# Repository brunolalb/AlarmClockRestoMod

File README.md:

# AlarmClockRestoMod
ESP32 Software for an Alarm Clock Resto Mod.

The idea is to use the components of an old alarm clock and replace the electronics with an ESP32, adding a lot of features to it. From an outside perspective, the clock will look as original as possible.

## Features

* WiFi connectivity
  * NTP time synchronization
  * Web server for advanced configuration
  * OTA updates
* Bluetooth connection from phone and to headphone/speaker
* Clock:
  * 7 segment display with dimming function
  * RTC for time keeping when power is out
* Alarms:
  * Configurable via web interface (advanced) or via buttons (only next alarm)
  * Configurable music or internet radio or buzzer for each alarm
  * Snooze function (delay configurable via web interface)
  * Vacation mode (turn off all alarms for a configurable period of time)
* Radio:
  * Internet radio stations configurable via web interface
  * Tuner button to switch between internet radio stations or playlists on microSD card
* microSD Card to store pre-owned Music, playlists and configuration files

## Components Overview
* Display is a 7 segment 4 digits with a TM1637, dimmable by software
* DS3231 for time keeping when power is out
* microSD Card with:
  * MP3 songs and playlists
  * Configuration file for radio stations (accepts internet radio station or playlist)
  * Configuration file for different alarms
* The tuner button of the alarm clock is a variable capacitor (10 - 500pF) read via a MPR121
  * Each frequency corresponds to an internet radio
* Bluetooth to connect to cellphone (play music from it) or to an external speaker/headphone
* Normal speaker connected via MAX98357A
* Buttons (Telefunken Digital Electronic 101):
  * 2 momentary switches to set time (Fast and slow)
  * 1 latching switch to turn on auto dimm/full light on display
  * 3 mutually-exclusive latching switches: show time, show next alarm (use the 2 momentary switches to set the alarm time) or "sleep mode" (turn on radio for 60min)
  * 1 momentary switch for sleep function (during alarm, press once to delay alarm in 5min, press twice to turn off alarm; during sleep mode, turn off radio)
  * 1 Volume slider (potentiometer)
  * 4 mutually-exclusive latching switches: turn on radio, turn off radio, alarm with radio, alarm with buzzing sound
  * 2 mutually-exclusive latching switches: radio corresponds to playlists, radio corresponds to internet radios
  * 1 momentary switch: one click (tries to connect to configured bluetooth speaker), two clicks (turns on bluetooth for phone to connect); if bluetooth connection is not successful after 1 min, turn off bluetooth
* Alarms:
  * fully configurable via web interface
  * choose days of the week
  * snooze time configurable
  * vacation mode
  * music and internet radio configured via web interface

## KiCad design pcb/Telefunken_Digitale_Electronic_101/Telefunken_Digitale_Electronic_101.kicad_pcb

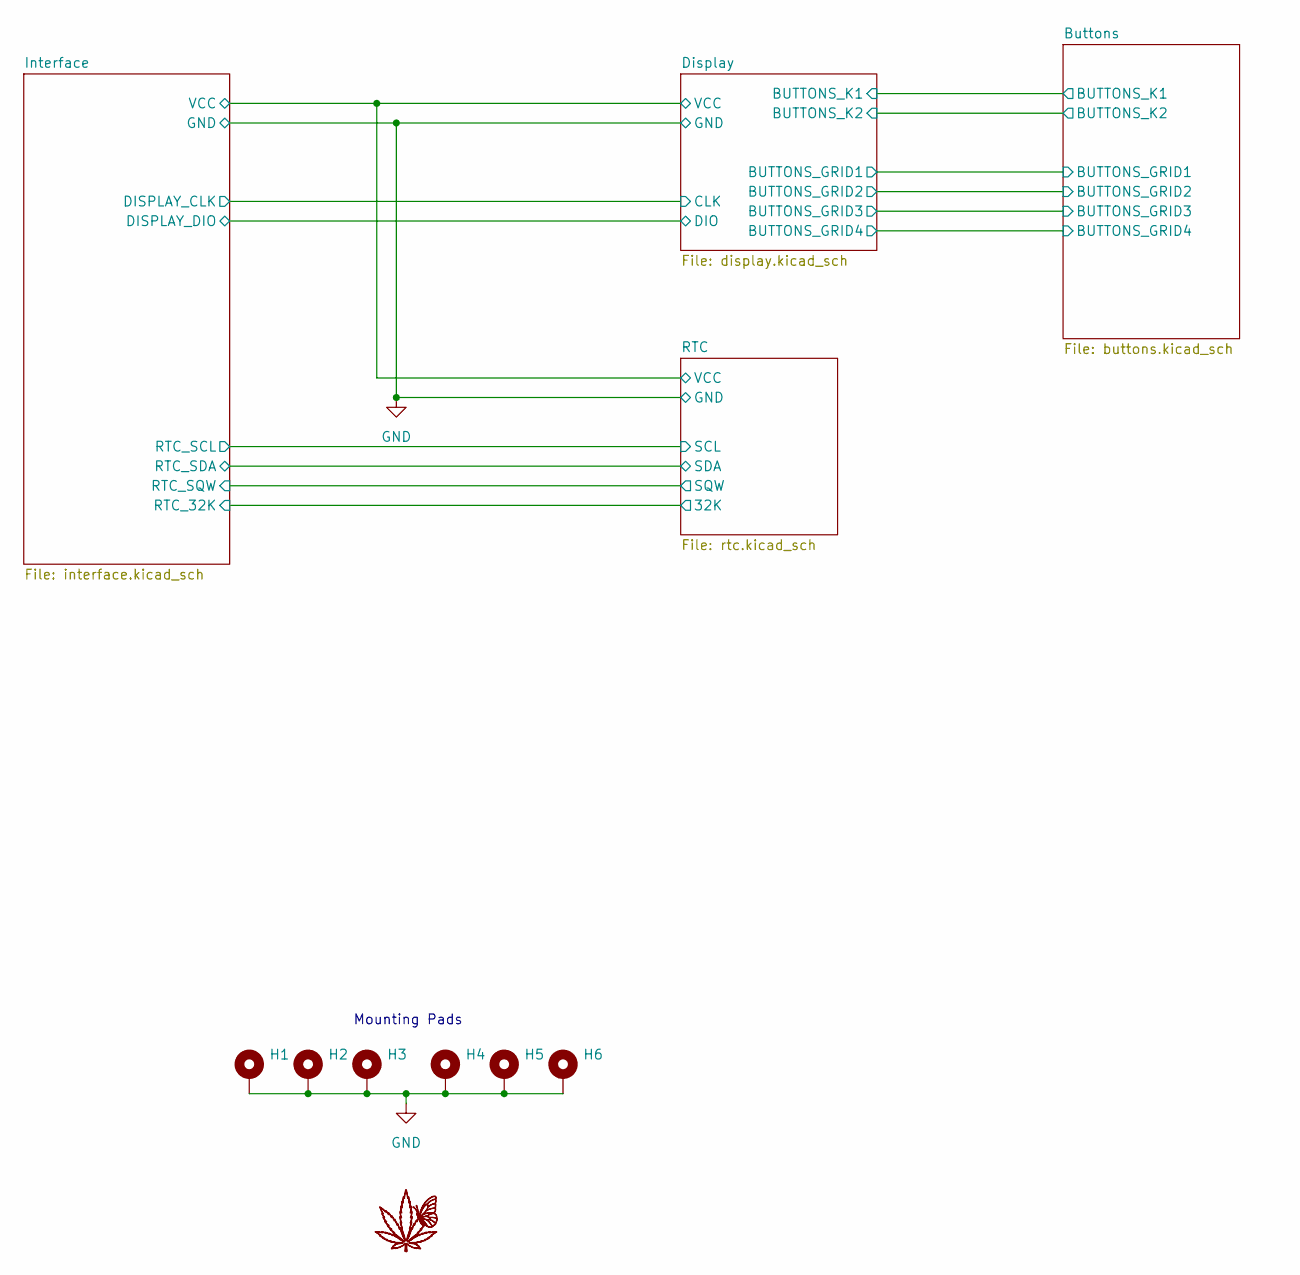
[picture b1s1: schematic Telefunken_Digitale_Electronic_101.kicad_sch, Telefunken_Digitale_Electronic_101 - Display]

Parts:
G1: LOGO
H1, H2, H3, H4, H5, H6: MountingHole_Pad_MP; BOARD_TO_BOARD_PAD_SMD

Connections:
GND: H1.MP (MP_MP), H2.MP (MP_MP), H3.MP (MP_MP), H4.MP (MP_MP), H5.MP (MP_MP), H6.MP (MP_MP); also elsewhere on the board

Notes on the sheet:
Mounting Pads

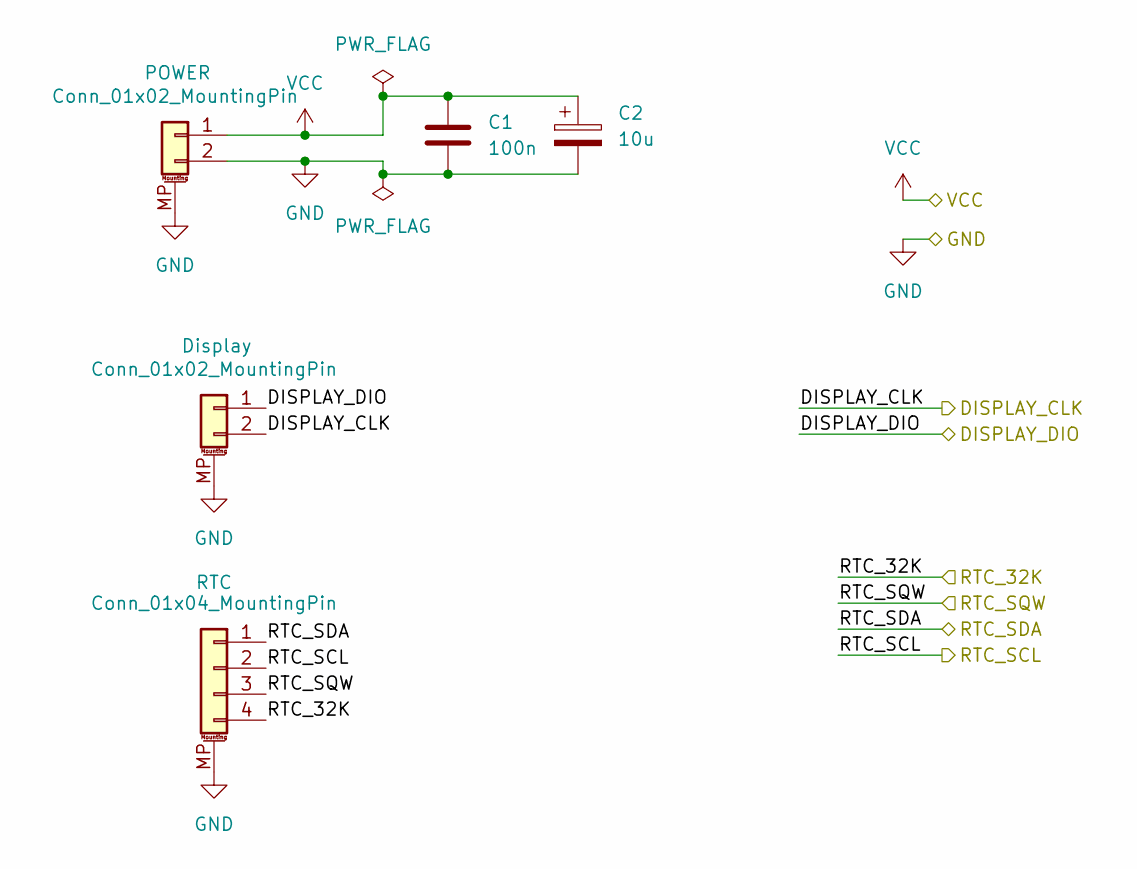
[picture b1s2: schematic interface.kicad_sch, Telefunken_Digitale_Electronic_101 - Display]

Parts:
C1: 100n; C_0603_1608Metric_Pad1.08x0.95mm_HandSolder
C2: 10u; CP_Radial_D4.0mm_P2.00mm
J1: Conn_01x02_MountingPin; JST_S2B-XH-SM4-TB
J2: Conn_01x02_MountingPin; Molex_PicoBlade_53261-0271_1x02-1MP_P1.25mm_Horizontal
J3: Conn_01x04_MountingPin; Molex_PicoBlade_53261-0471_1x04-1MP_P1.25mm_Horizontal

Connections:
/Display/CLK: J2.2; also elsewhere on the board
/Display/DIO: J2.1; also elsewhere on the board
/Interface/RTC_32K: J3.4; also elsewhere on the board
/Interface/RTC_SCL: J3.2; also elsewhere on the board
/Interface/RTC_SDA: J3.1; also elsewhere on the board
/Interface/RTC_SQW: J3.3; also elsewhere on the board
GND: C1.2, C2.2, J1.2, J1.MP (MountPin), J2.MP (MountPin), J3.MP (MountPin); also elsewhere on the board
VCC: C1.1, C2.1, J1.1; also elsewhere on the board

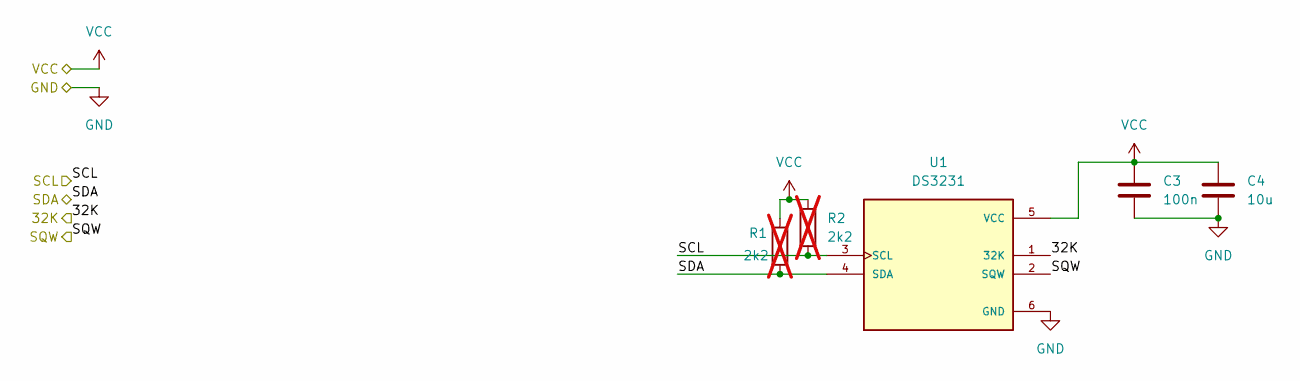
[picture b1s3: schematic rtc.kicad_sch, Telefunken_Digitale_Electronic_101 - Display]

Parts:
C3: 100n; C_0603_1608Metric_Pad1.08x0.95mm_HandSolder
C4: 10u; C_0805_2012Metric_Pad1.18x1.45mm_HandSolder
R1, R2: 2k2; R_0603_1608Metric_Pad0.98x0.95mm_HandSolder; not fitted
U1: DS3231

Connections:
/Interface/RTC_32K: U1.1 (32K); also elsewhere on the board
/Interface/RTC_SCL: R2.2, U1.3 (SCL); also elsewhere on the board
/Interface/RTC_SDA: R1.2, U1.4 (SDA); also elsewhere on the board
/Interface/RTC_SQW: U1.2 (SQW); also elsewhere on the board
GND: C3.2, C4.2, U1.6 (GND); also elsewhere on the board
VCC: C3.1, C4.1, R1.1, R2.1, U1.5 (VCC); also elsewhere on the board

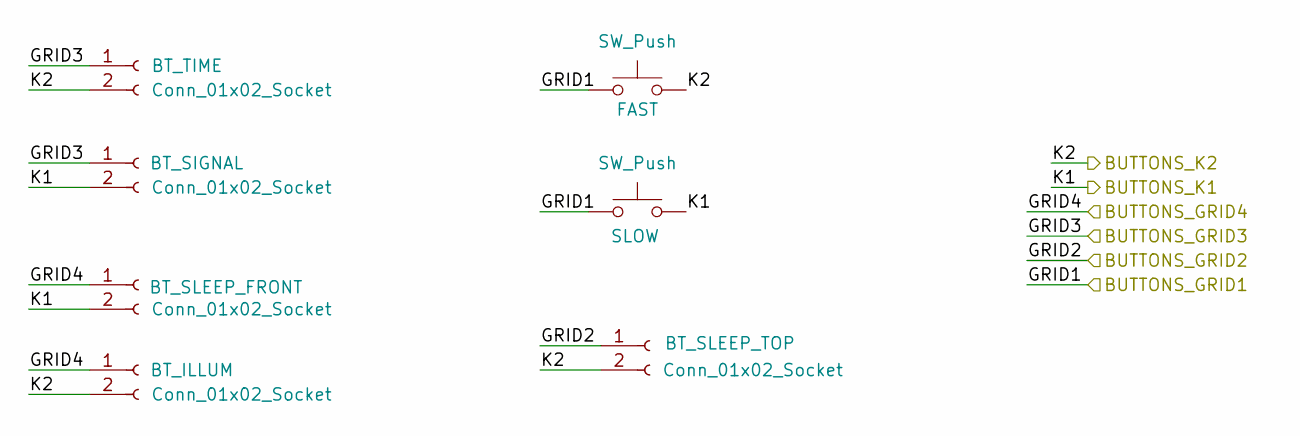
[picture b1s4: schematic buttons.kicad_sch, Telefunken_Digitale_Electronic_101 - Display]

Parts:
J4, J5, J6, J7, J8: Conn_01x02_Socket; PinSocket_1x02_P2.54mm_Vertical
SW1, SW2: SW_Push; TACT_SWITCH_3.2X4.2X2.5MM

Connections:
/Buttons/GRID1: SW1.1, SW2.1; also elsewhere on the board
/Buttons/GRID2: J8.1; also elsewhere on the board
/Buttons/GRID3: J4.1, J5.1; also elsewhere on the board
/Buttons/GRID4: J6.1, J7.1; also elsewhere on the board
/Buttons/K1: J5.2, J6.2, SW2.2; also elsewhere on the board
/Buttons/K2: J4.2, J7.2, J8.2, SW1.2; also elsewhere on the board

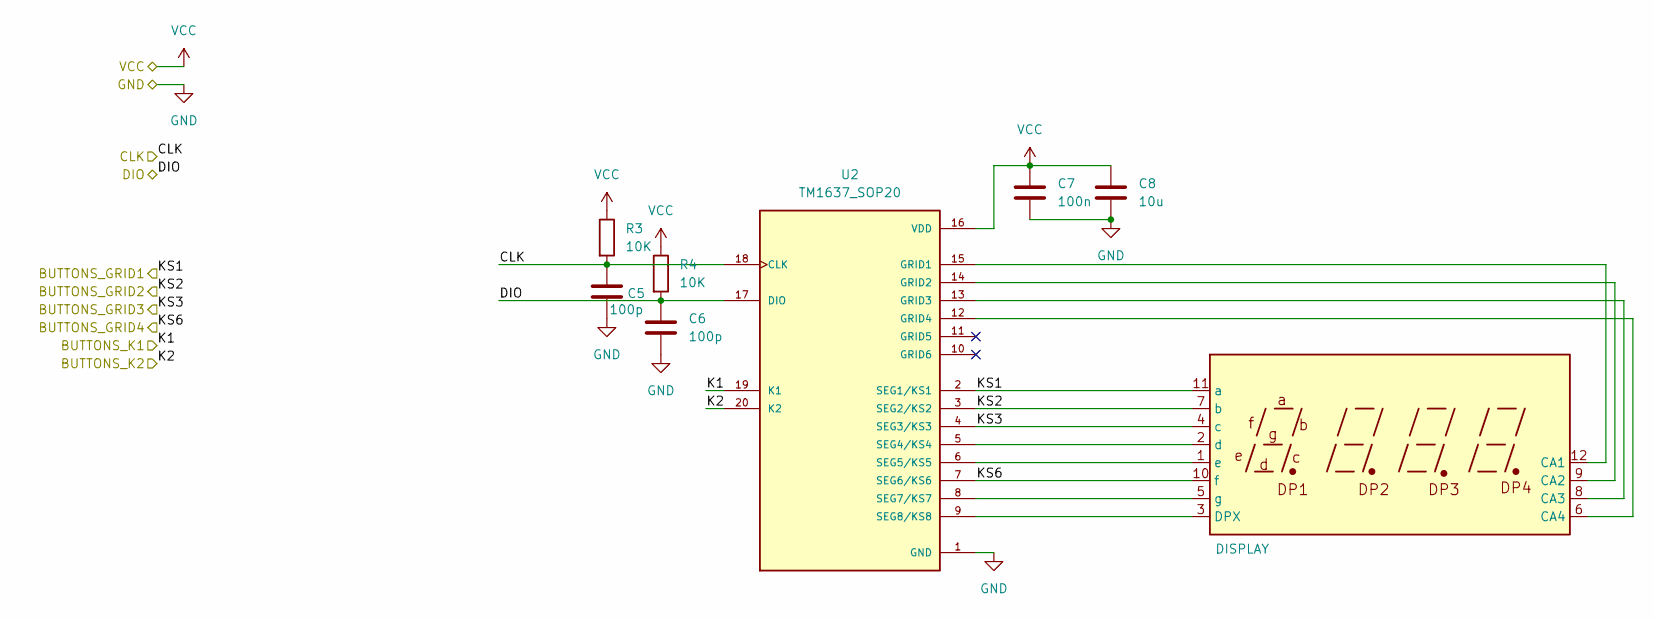
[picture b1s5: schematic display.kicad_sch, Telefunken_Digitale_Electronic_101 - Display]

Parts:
C5, C6: 100p; C_0603_1608Metric_Pad1.08x0.95mm_HandSolder
C7: 100n; C_0603_1608Metric_Pad1.08x0.95mm_HandSolder
C8: 10u; C_0805_2012Metric_Pad1.18x1.45mm_HandSolder
DISPLAY1: 8041BS-1
R3, R4: 10K; R_0603_1608Metric_Pad0.98x0.95mm_HandSolder
U2: TM1637_SOP20; SOIC127P1035X255-20N

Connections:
/Buttons/GRID1: DISPLAY1.11 (a), U2.2 (SEG1/KS1); also elsewhere on the board
/Buttons/GRID2: DISPLAY1.7 (b), U2.3 (SEG2/KS2); also elsewhere on the board
/Buttons/GRID3: DISPLAY1.4 (c), U2.4 (SEG3/KS3); also elsewhere on the board
/Buttons/GRID4: DISPLAY1.10 (f), U2.7 (SEG6/KS6); also elsewhere on the board
/Buttons/K1: U2.19 (K1); also elsewhere on the board
/Buttons/K2: U2.20 (K2); also elsewhere on the board
/Display/CLK: C5.1, R3.2, U2.18 (CLK); also elsewhere on the board
/Display/DIO: C6.1, R4.2, U2.17 (DIO); also elsewhere on the board
GND: C5.2, C6.2, C7.2, C8.2, U2.1 (GND); also elsewhere on the board
unnamed: DISPLAY1.12 (CA1), U2.15 (GRID1)
unnamed: DISPLAY1.9 (CA2), U2.14 (GRID2)
unnamed: DISPLAY1.8 (CA3), U2.13 (GRID3)
unnamed: DISPLAY1.6 (CA4), U2.12 (GRID4)
unnamed: DISPLAY1.3 (DPX), U2.9 (SEG8/KS8)
unnamed: DISPLAY1.2 (d), U2.5 (SEG4/KS4)
unnamed: DISPLAY1.1 (e), U2.6 (SEG5/KS5)
unnamed: DISPLAY1.5 (g), U2.8 (SEG7/KS7)
VCC: C7.1, C8.1, R3.1, R4.1, U2.16 (VDD); also elsewhere on the board

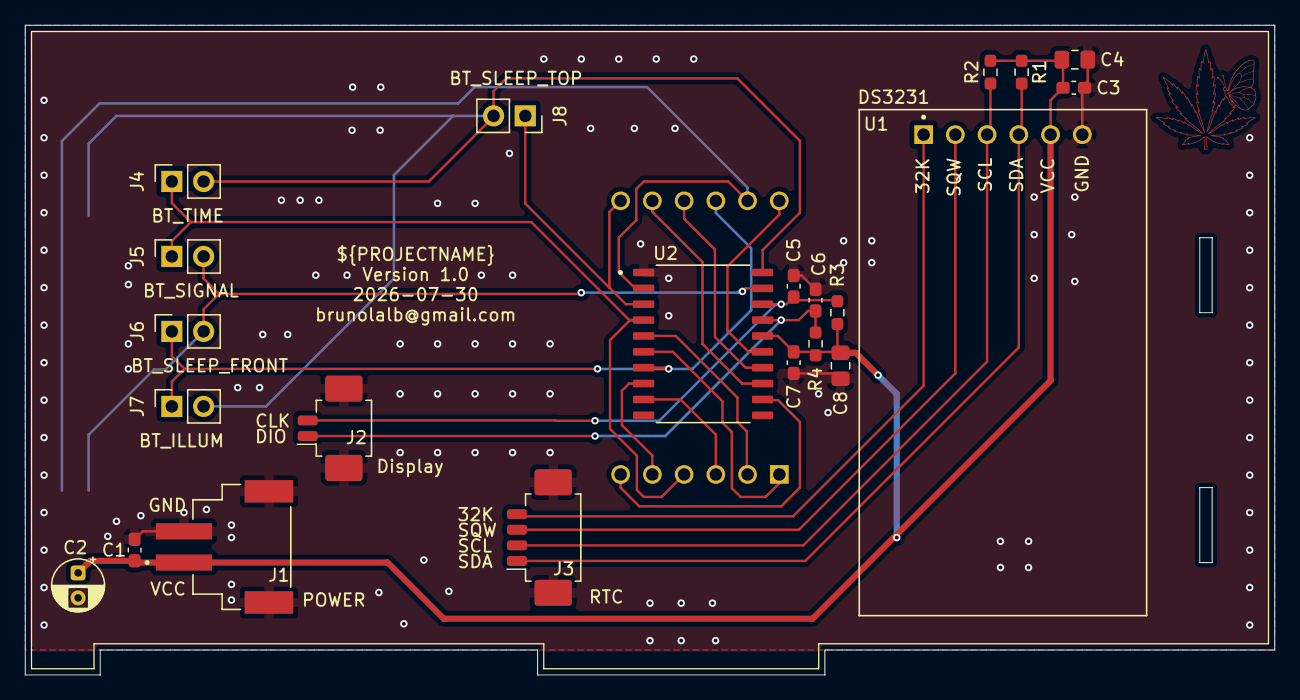
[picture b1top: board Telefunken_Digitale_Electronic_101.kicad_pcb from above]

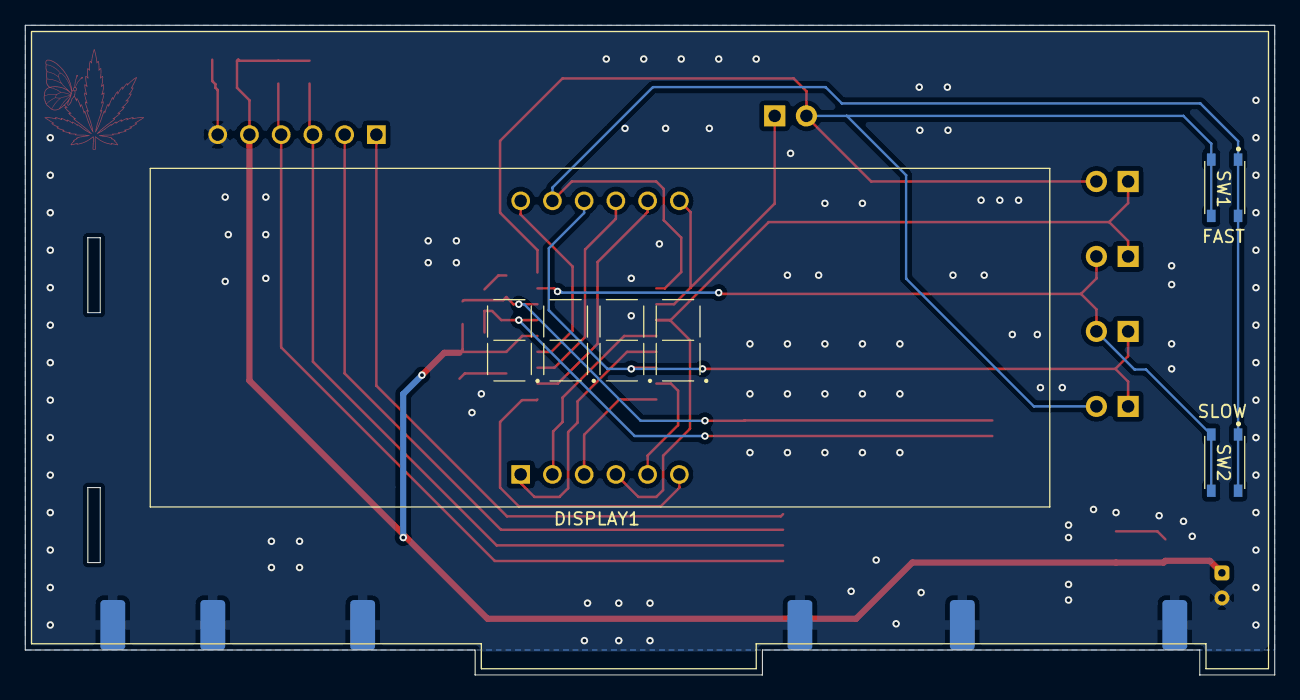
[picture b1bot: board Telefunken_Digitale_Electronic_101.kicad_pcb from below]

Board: 2 copper layers, 100.0 x 52.0 mm, 32 parts (9 on the bottom side), 22 nets.

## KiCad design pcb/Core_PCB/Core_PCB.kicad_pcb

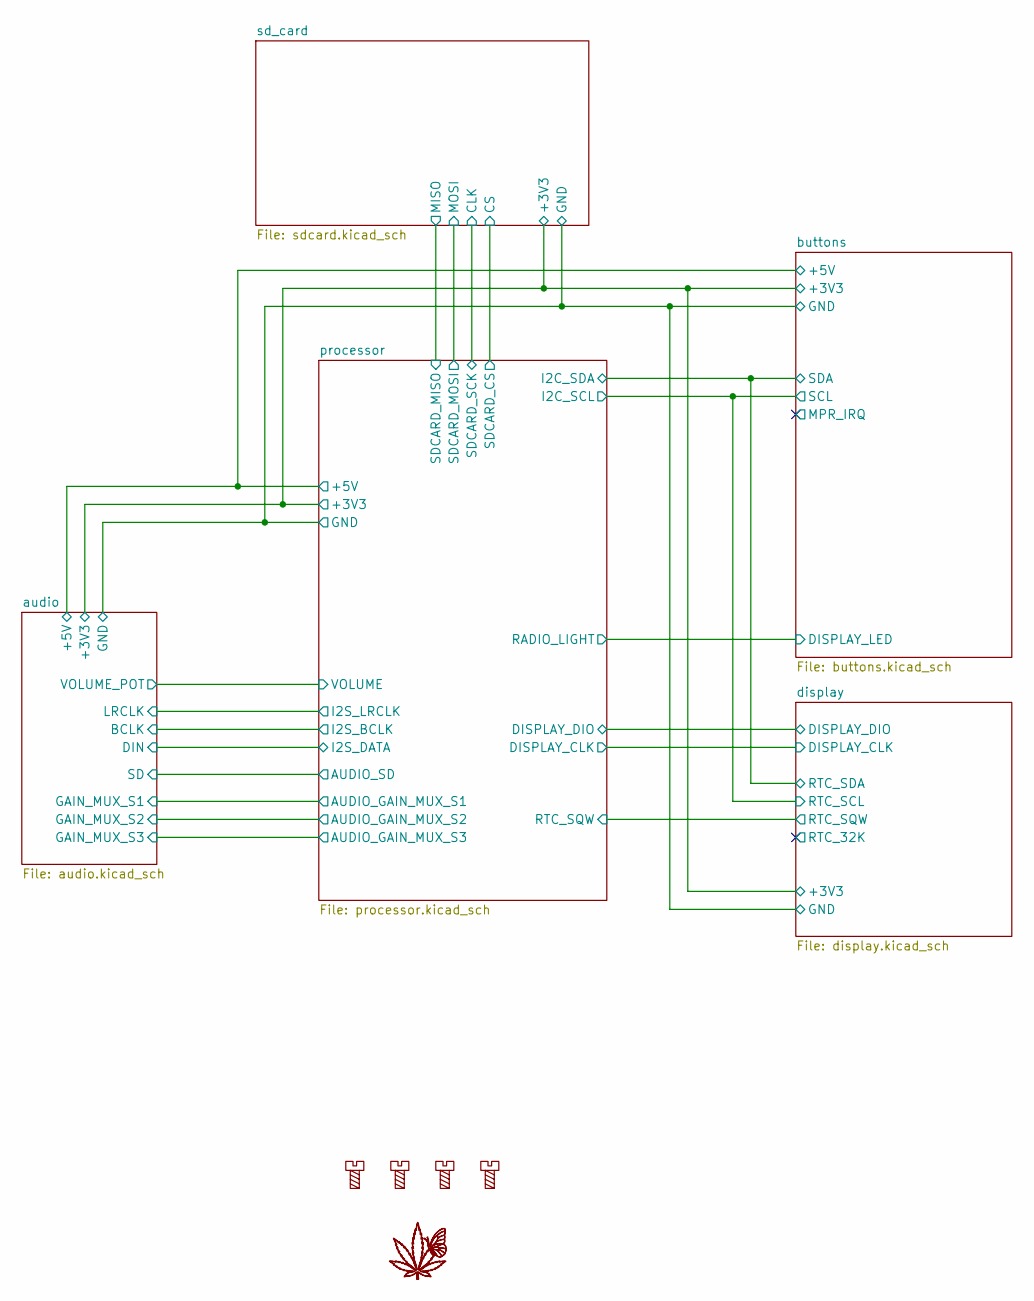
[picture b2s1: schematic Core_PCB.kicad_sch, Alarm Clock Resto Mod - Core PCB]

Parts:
G1: LOGO
H1, H2, H3, H4: MountingScrew; MountingHole_3.2mm_M3

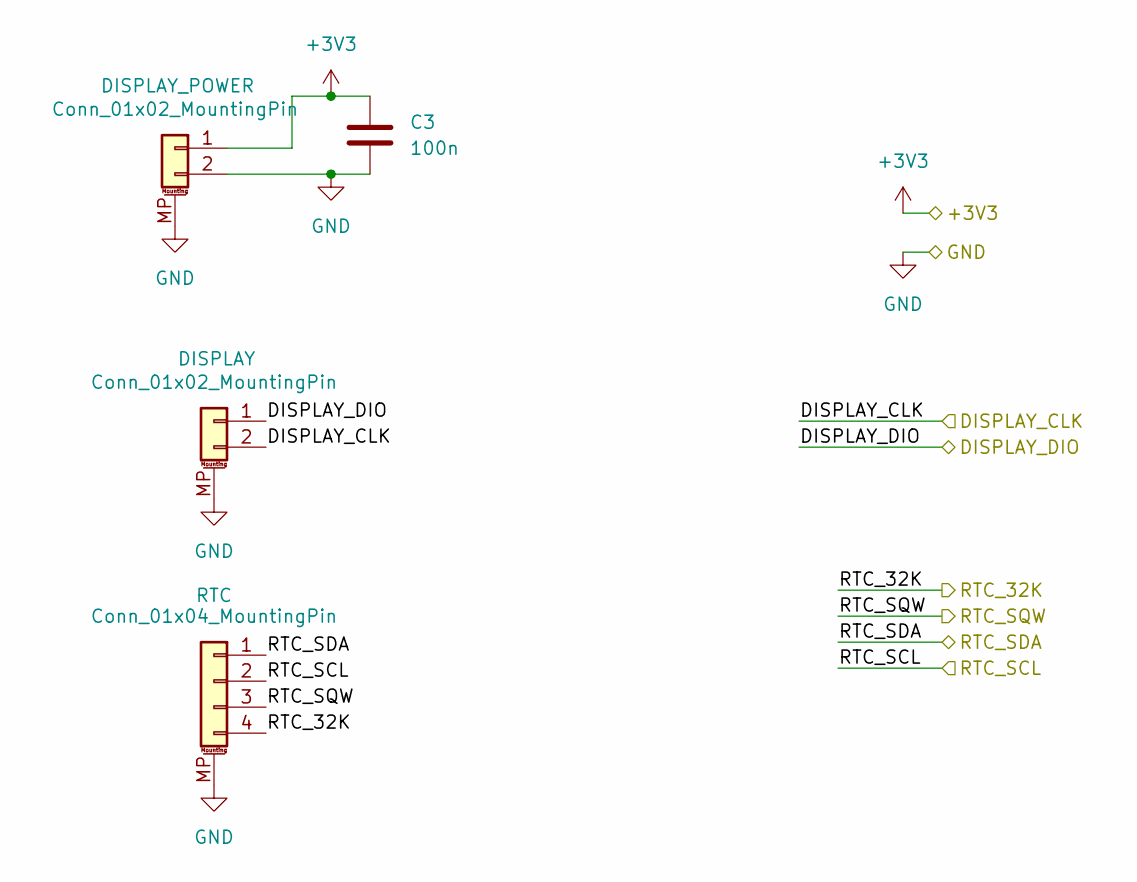
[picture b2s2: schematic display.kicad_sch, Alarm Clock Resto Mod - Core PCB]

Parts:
C3: 100n; C_0603_1608Metric_Pad1.08x0.95mm_HandSolder
J2: Conn_01x02_MountingPin; JST_S2B-XH-SM4-TB
J3: Conn_01x02_MountingPin; Molex_PicoBlade_53261-0271_1x02-1MP_P1.25mm_Horizontal
J4: Conn_01x04_MountingPin; Molex_PicoBlade_53261-0471_1x04-1MP_P1.25mm_Horizontal

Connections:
+3V3: C3.1, J2.1; also elsewhere on the board
/buttons/SCL: J4.2; also elsewhere on the board
/buttons/SDA: J4.1; also elsewhere on the board
/display/DISPLAY_CLK: J3.2; also elsewhere on the board
/display/DISPLAY_DIO: J3.1; also elsewhere on the board
/display/RTC_32K: J4.4
/display/RTC_SQW: J4.3; also elsewhere on the board
GND: C3.2, J2.2, J2.MP (MountPin), J3.MP (MountPin), J4.MP (MountPin); also elsewhere on the board

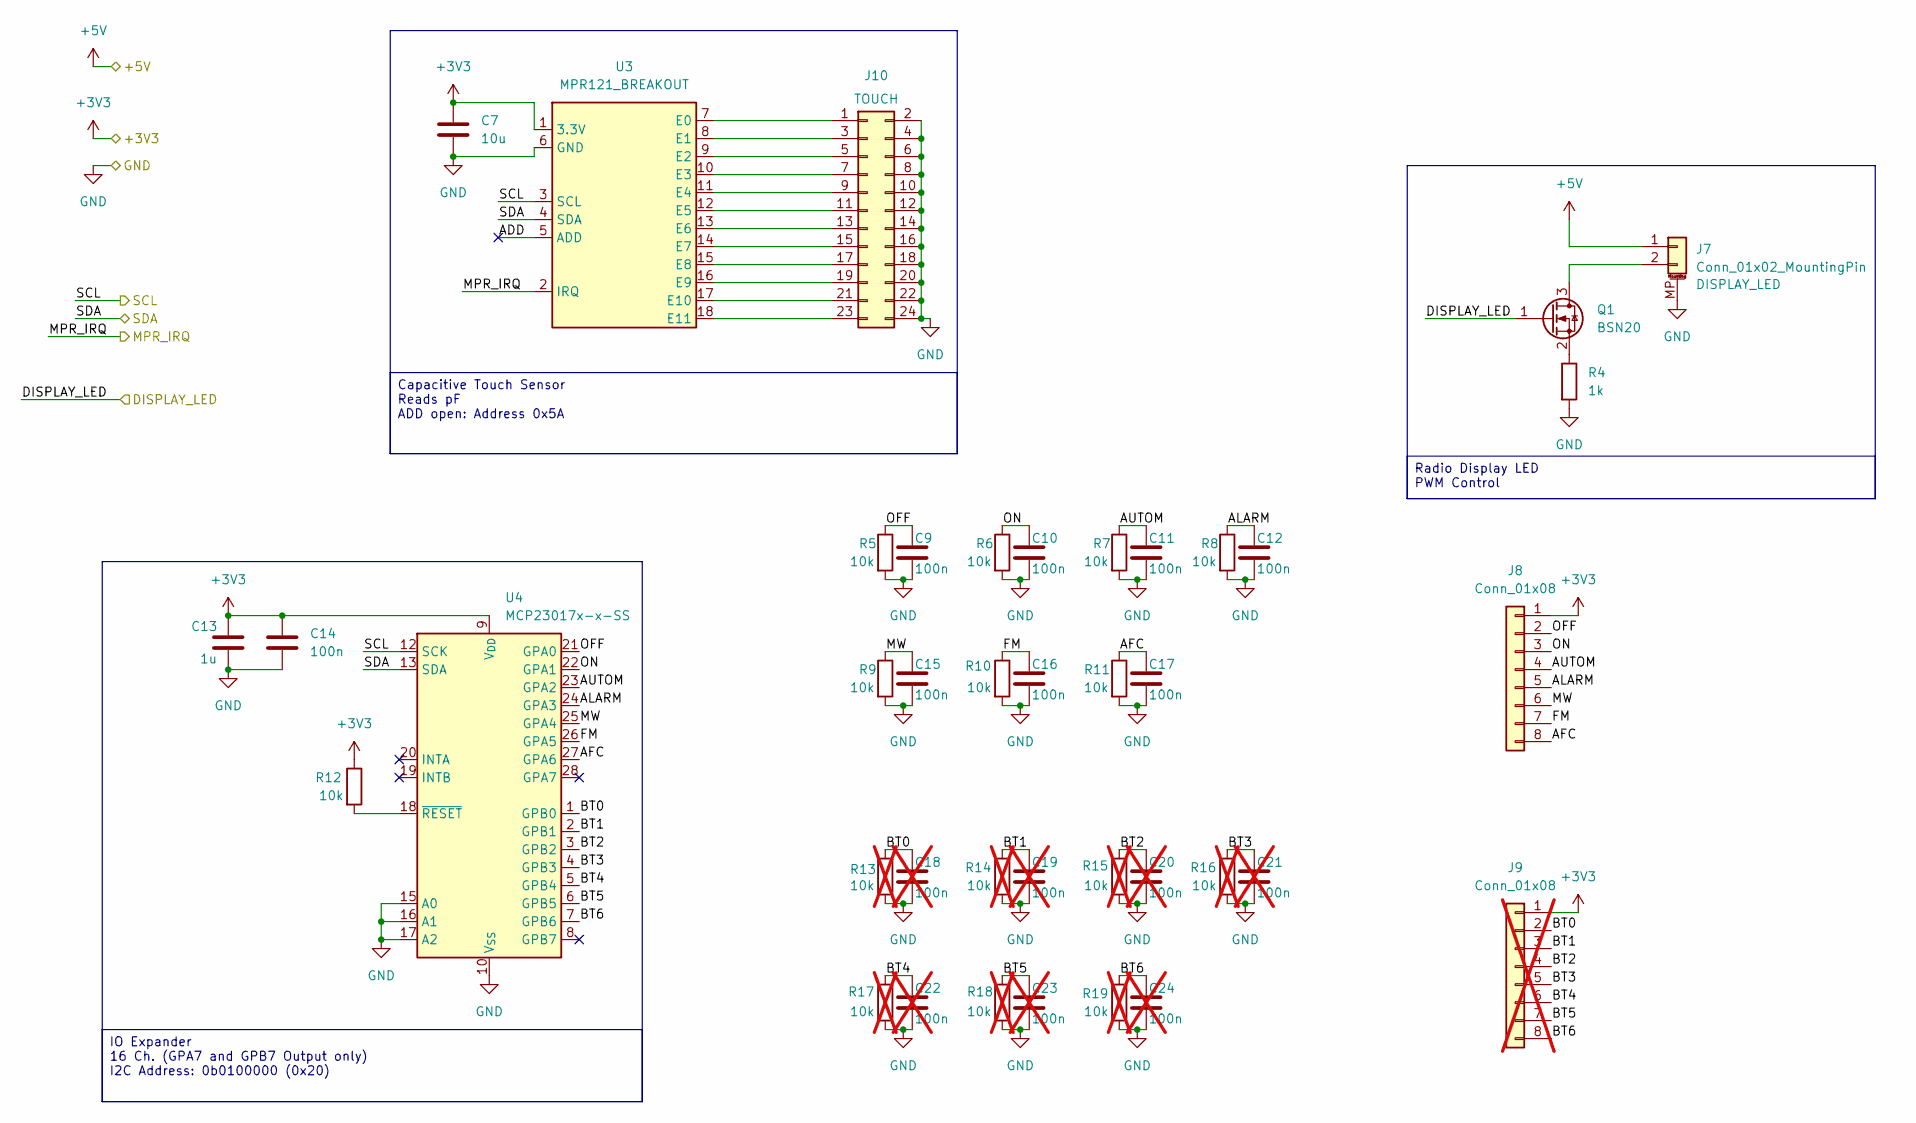
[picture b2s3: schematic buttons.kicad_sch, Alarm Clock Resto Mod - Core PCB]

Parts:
C7: 10u; C_0805_2012Metric_Pad1.18x1.45mm_HandSolder
C9, C10, C11, C12, C14, C15, C16, C17: 100n; C_0603_1608Metric_Pad1.08x0.95mm_HandSolder
C13: 1u; C_0805_2012Metric_Pad1.18x1.45mm_HandSolder
C18, C19, C20, C21, C22, C23, C24: 100n; C_0603_1608Metric_Pad1.08x0.95mm_HandSolder; not fitted
J7: Conn_01x02_MountingPin; JST_S2B-XH-SM4-TB
J8: Conn_01x08; PinSocket_1x08_P2.54mm_Vertical
J9: Conn_01x08; PinSocket_1x08_P2.54mm_Vertical; not fitted
J10: Conn_02x12_Odd_Even; PinSocket_2x12_P2.54mm_Vertical
Q1: BSN20; SOT-23
R4: 1k; R_0603_1608Metric_Pad0.98x0.95mm_HandSolder
R5, R6, R7, R8, R9, R10, R11, R12: 10k; R_0603_1608Metric_Pad0.98x0.95mm_HandSolder
R13, R14, R15, R16, R17, R18, R19: 10k; R_0603_1608Metric_Pad0.98x0.95mm_HandSolder; not fitted
U3: MPR121_BREAKOUT
U4: MCP23017x-x-SS; SSOP-28_5.3x10.2mm_P0.65mm

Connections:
+3V3: C7.1, C13.1, C14.1, J8.1, J9.1, R12.1, U3.1 (3.3V), U4.9 (V_{DD}); also elsewhere on the board
+5V: J7.1; also elsewhere on the board
/buttons/ADD: U3.5 (ADD)
/buttons/AFC: C17.1, J8.8, R11.1, U4.27 (GPA6)
/buttons/ALARM: C12.1, J8.5, R8.1, U4.24 (GPA3)
/buttons/AUTOM: C11.1, J8.4, R7.1, U4.23 (GPA2)
/buttons/BT0: C18.1, J9.2, R13.1, U4.1 (GPB0)
/buttons/BT1: C19.1, J9.3, R14.1, U4.2 (GPB1)
/buttons/BT2: C20.1, J9.4, R15.1, U4.3 (GPB2)
/buttons/BT3: C21.1, J9.5, R16.1, U4.4 (GPB3)
/buttons/BT4: C22.1, J9.6, R17.1, U4.5 (GPB4)
/buttons/BT5: C23.1, J9.7, R18.1, U4.6 (GPB5)
/buttons/BT6: C24.1, J9.8, R19.1, U4.7 (GPB6)
/buttons/DISPLAY_LED: Q1.1 (G); also elsewhere on the board
/buttons/FM: C16.1, J8.7, R10.1, U4.26 (GPA5)
/buttons/MPR_IRQ: U3.2 (IRQ)
/buttons/MW: C15.1, J8.6, R9.1, U4.25 (GPA4)
/buttons/OFF: C9.1, J8.2, R5.1, U4.21 (GPA0)
/buttons/ON: C10.1, J8.3, R6.1, U4.22 (GPA1)
/buttons/SCL: U3.3 (SCL), U4.12 (SCK); also elsewhere on the board
/buttons/SDA: U3.4 (SDA), U4.13 (SDA); also elsewhere on the board
GND: C7.2, C9.2, C10.2, C11.2, C12.2, C13.2, C14.2, C15.2, C16.2, C17.2, C18.2, C19.2, C20.2, C21.2, C22.2, C23.2, C24.2, J7.MP (MountPin), J10.2, J10.4, J10.6, J10.8, J10.10, J10.12, J10.14, J10.16, J10.18, J10.20, J10.22, J10.24, R4.2, R5.2, R6.2, R7.2, R8.2, R9.2, R10.2, R11.2, R13.2, R14.2, R15.2, R16.2, R17.2, R18.2, R19.2, U3.6 (GND), U4.10 (V_{SS}), U4.15 (A0), U4.16 (A1), U4.17 (A2); also elsewhere on the board
unnamed: J7.2, Q1.3 (D)
unnamed: J10.1, U3.7 (E0)
unnamed: J10.3, U3.8 (E1)
unnamed: J10.5, U3.9 (E2)
unnamed: J10.7, U3.10 (E3)
unnamed: J10.9, U3.11 (E4)
unnamed: J10.11, U3.12 (E5)
unnamed: J10.13, U3.13 (E6)
unnamed: J10.15, U3.14 (E7)
unnamed: J10.17, U3.15 (E8)
unnamed: J10.19, U3.16 (E9)
unnamed: J10.21, U3.17 (E10)
unnamed: J10.23, U3.18 (E11)
unnamed: Q1.2 (S), R4.1
unnamed: R12.2, U4.18 (~RESET)

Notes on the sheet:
Capacitive Touch Sensor Reads pF ADD open: Address 0x5A
IO Expander 16 Ch. (GPA7 and GPB7 Output only) I2C Address: 0b0100000 (0x20)
Radio Display LED PWM Control

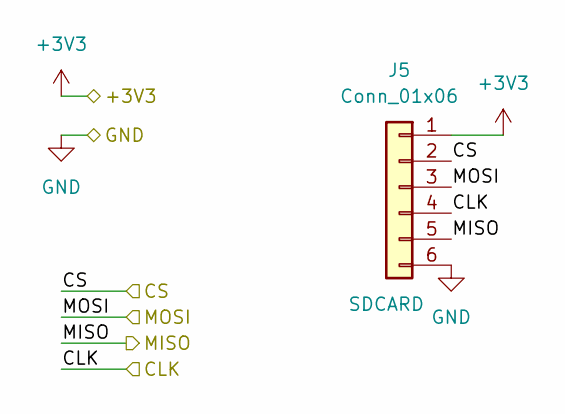
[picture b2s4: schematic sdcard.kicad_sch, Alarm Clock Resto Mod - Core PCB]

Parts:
J5: Conn_01x06; PinSocket_1x06_P2.54mm_Vertical

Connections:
+3V3: J5.1; also elsewhere on the board
/processor/SDCARD_CS: J5.2; also elsewhere on the board
/processor/SDCARD_MISO: J5.5; also elsewhere on the board
/processor/SDCARD_MOSI: J5.3; also elsewhere on the board
/processor/SDCARD_SCK: J5.4; also elsewhere on the board
GND: J5.6; also elsewhere on the board

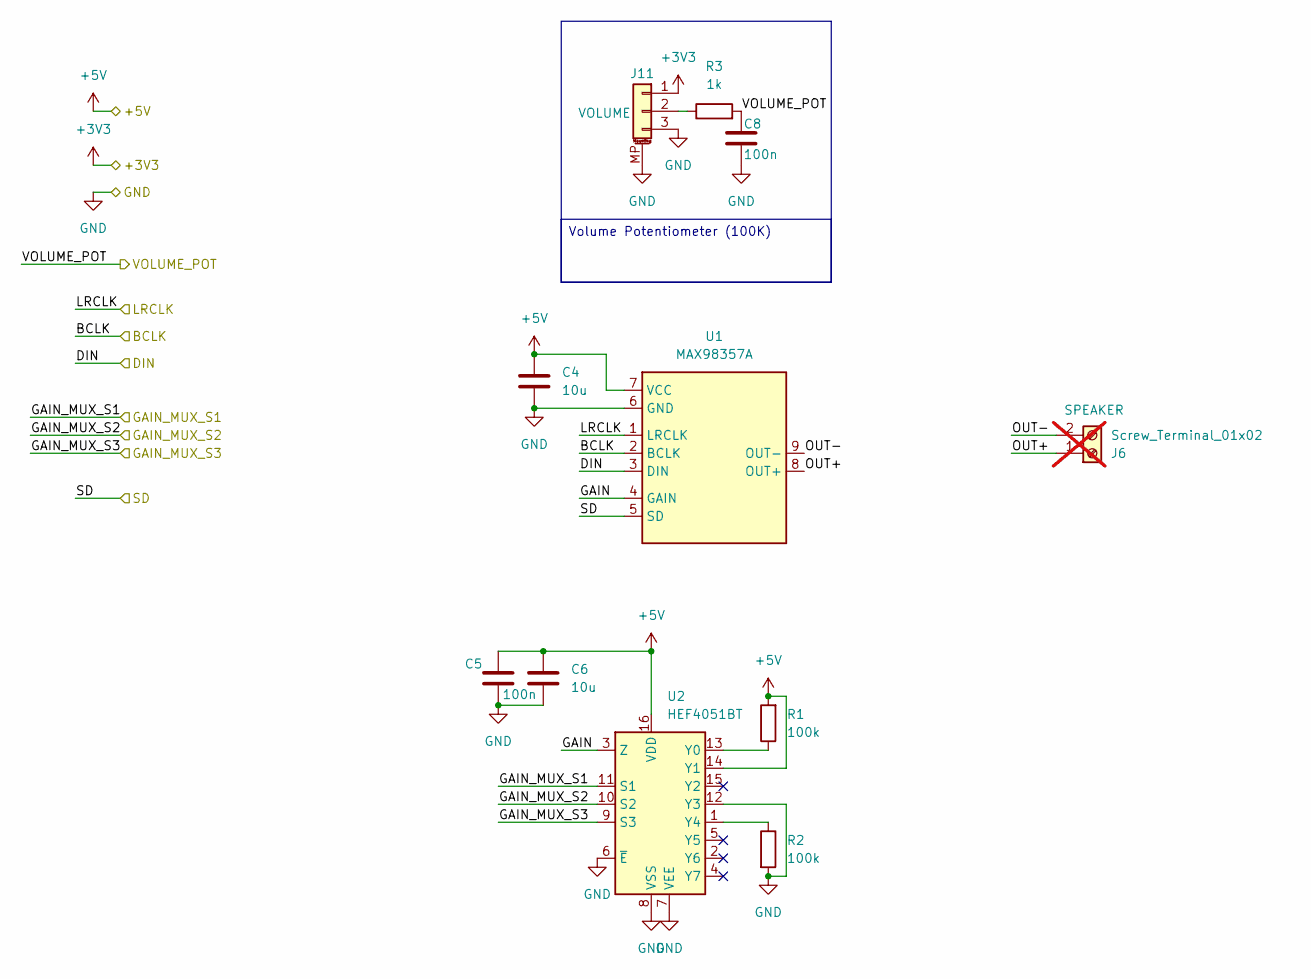
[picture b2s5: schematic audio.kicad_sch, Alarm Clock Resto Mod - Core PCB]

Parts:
C4, C6: 10u; C_0805_2012Metric_Pad1.18x1.45mm_HandSolder
C5, C8: 100n; C_0603_1608Metric_Pad1.08x0.95mm_HandSolder
J6: Screw_Terminal_01x02; TerminalBlock_Phoenix_PT-1,5-2-3.5-H_1x02_P3.50mm_Horizontal; not fitted
J11: Conn_01x03_MountingPin; Molex_PicoBlade_53261-0371_1x03-1MP_P1.25mm_Horizontal
R1, R2: 100k; R_0603_1608Metric_Pad0.98x0.95mm_HandSolder
R3: 1k; R_0603_1608Metric_Pad0.98x0.95mm_HandSolder
U1: MAX98357A; MAX98357A_Adafruit
U2: HEF4051BT; SOIC-16_3.9x9.9mm_P1.27mm

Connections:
+3V3: J11.1; also elsewhere on the board
+5V: C4.1, C5.1, C6.1, R1.2, U1.7 (VCC), U2.14 (Y1), U2.16 (VDD); also elsewhere on the board
/audio/BCLK: U1.2 (BCLK); also elsewhere on the board
/audio/DIN: U1.3 (DIN); also elsewhere on the board
/audio/GAIN: U1.4 (GAIN), U2.3 (Z)
/audio/GAIN_MUX_S1: U2.11 (S1); also elsewhere on the board
/audio/GAIN_MUX_S2: U2.10 (S2); also elsewhere on the board
/audio/GAIN_MUX_S3: U2.9 (S3); also elsewhere on the board
/audio/LRCLK: U1.1 (LRCLK); also elsewhere on the board
/audio/OUT+: J6.1, U1.8 (OUT+)
/audio/OUT-: J6.2, U1.9 (OUT-)
/audio/SD: U1.5 (SD); also elsewhere on the board
/audio/VOLUME_POT: C8.1, R3.2; also elsewhere on the board
GND: C4.2, C5.2, C6.2, C8.2, J11.3, J11.MP (MountPin), R2.2, U1.6 (GND), U2.6 (~E), U2.7 (VEE), U2.8 (VSS), U2.12 (Y3); also elsewhere on the board
unnamed: J11.2, R3.1
unnamed: R1.1, U2.13 (Y0)
unnamed: R2.1, U2.1 (Y4)

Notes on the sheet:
Volume Potentiometer (100K)

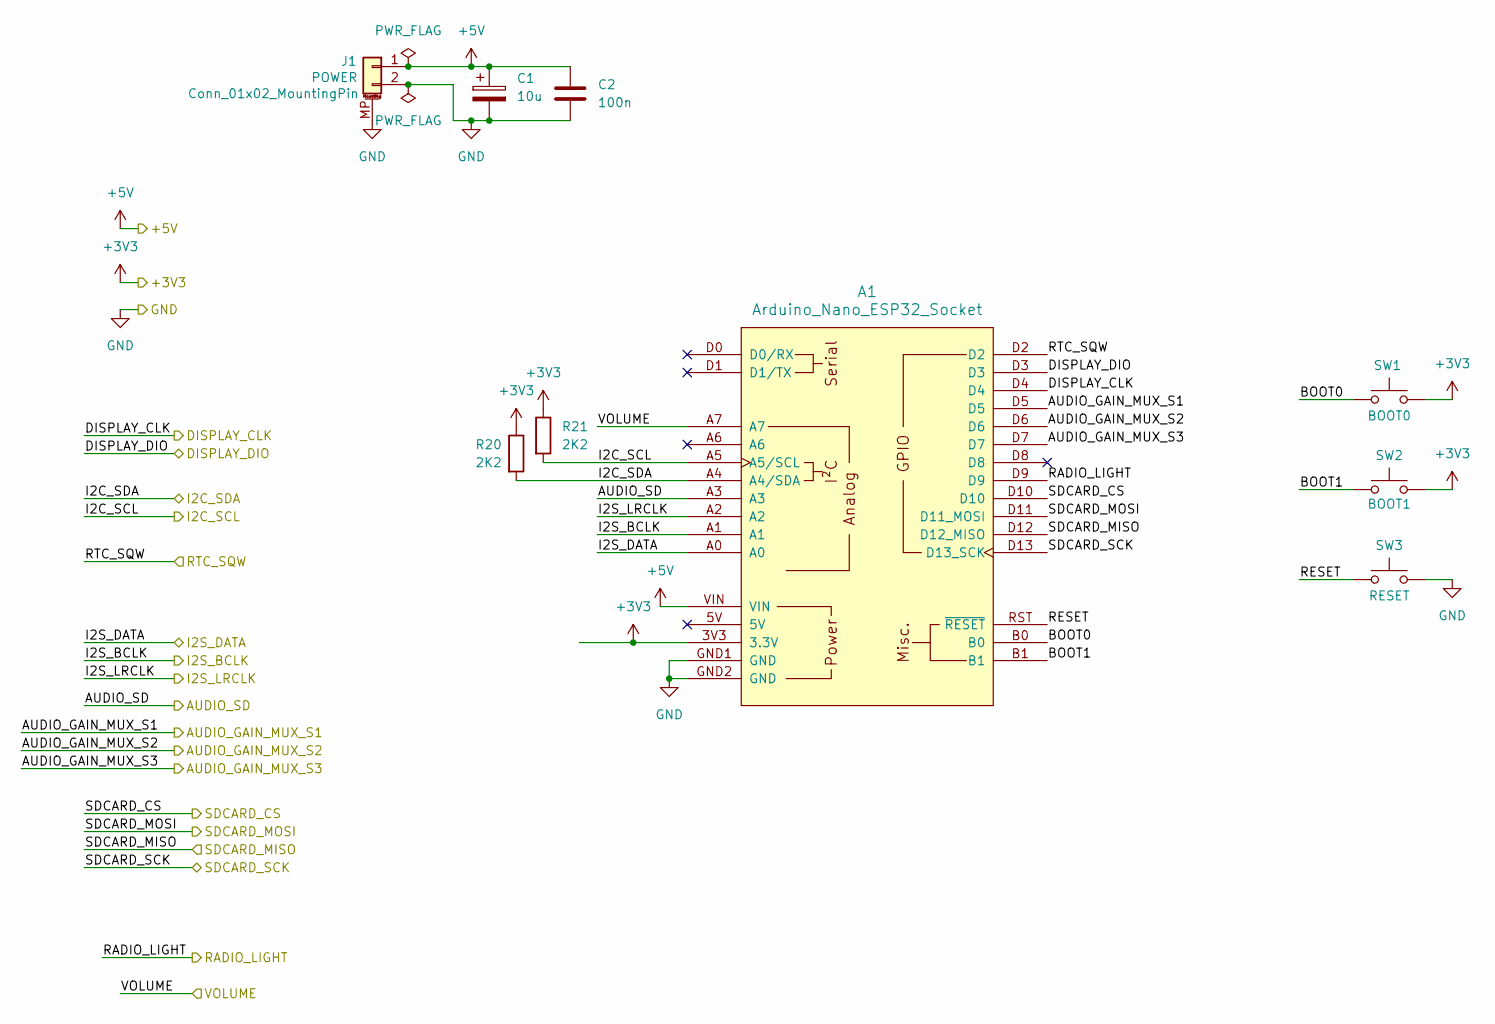
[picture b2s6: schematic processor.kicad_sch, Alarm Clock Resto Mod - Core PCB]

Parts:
A1: Arduino_Nano_ESP32_Socket
C1: 10u; CP_Radial_D4.0mm_P2.00mm
C2: 100n; C_0603_1608Metric_Pad1.08x0.95mm_HandSolder
J1: Conn_01x02_MountingPin; JST_S2B-XH-SM4-TB
R20, R21: 2K2; R_0603_1608Metric_Pad0.98x0.95mm_HandSolder
SW1, SW2, SW3: SW_Push; SW_PUSH_6mm

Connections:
+3V3: A1.3V3 (3.3V), R20.1, R21.1, SW1.2, SW2.2; also elsewhere on the board
+5V: A1.VIN, C1.1, C2.1, J1.1; also elsewhere on the board
/audio/BCLK: A1.A1; also elsewhere on the board
/audio/DIN: A1.A0; also elsewhere on the board
/audio/GAIN_MUX_S1: A1.D5; also elsewhere on the board
/audio/GAIN_MUX_S2: A1.D6; also elsewhere on the board
/audio/GAIN_MUX_S3: A1.D7; also elsewhere on the board
/audio/LRCLK: A1.A2; also elsewhere on the board
/audio/SD: A1.A3; also elsewhere on the board
/audio/VOLUME_POT: A1.A7; also elsewhere on the board
/buttons/DISPLAY_LED: A1.D9; also elsewhere on the board
/buttons/SCL: A1.A5 (A5/SCL), R21.2; also elsewhere on the board
/buttons/SDA: A1.A4 (A4/SDA), R20.2; also elsewhere on the board
/display/DISPLAY_CLK: A1.D4; also elsewhere on the board
/display/DISPLAY_DIO: A1.D3; also elsewhere on the board
/display/RTC_SQW: A1.D2; also elsewhere on the board
/processor/BOOT0: A1.B0, SW1.1
/processor/BOOT1: A1.B1, SW2.1
/processor/RESET: A1.RST (~RESET), SW3.1
/processor/SDCARD_CS: A1.D10; also elsewhere on the board
/processor/SDCARD_MISO: A1.D12 (D12_MISO); also elsewhere on the board
/processor/SDCARD_MOSI: A1.D11 (D11_MOSI); also elsewhere on the board
/processor/SDCARD_SCK: A1.D13 (D13_SCK); also elsewhere on the board
GND: A1.GND1 (GND), A1.GND2 (GND), C1.2, C2.2, J1.2, J1.MP (MountPin), SW3.2; also elsewhere on the board
